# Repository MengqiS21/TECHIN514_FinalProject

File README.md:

# Pet Activity & Proximity Tracker

A wearable sensing tag for pets and a tabletop display that visualizes daily activity and proximity-based companionship.  
The system is designed as a calm, ambient tool that supports reflection rather than real-time alerts, helping pet owners understand patterns of activity and togetherness over the course of a day. By translating sensed data into a physical gauge, the project emphasizes presence and routine over precise tracking or notifications.

## 1. Overview

### What it does
This project consists of a lightweight sensing device attached to a pet’s collar and a tabletop display device placed in the home. The system tracks the pet’s activity level and estimates proximity to the owner throughout the day, visualizing overall “bond time” using a physical gauge instead of a screen.

### General system sketch

### Repository structure
```text
TECHIN514_FinalProject/
├─ README.md
├─ archive/
│  └─ root_pio_legacy/          # early PlatformIO prototype
├─ docs/
│  ├─ images/                   # system diagrams and renders
│  ├─ datasheets/               # component datasheets
│  └─ gantt.xlsx
├─ firmware/
│  ├─ sensor_tag/               # collar sensing tag firmware (ESP32-C3)
│  │  ├─ src/
│  │  ├─ include/
│  │  ├─ lib/
│  │  └─ test/
│  └─ display_meter/            # tabletop display firmware (ESP32-C3)
│     ├─ src/
│     ├─ include/
│     ├─ lib/
│     └─ test/
└─ hardware/
   ├─ pcb/
   │  ├─ sensor_tag/            # sensor-tag PCB project files
   │  ├─ display/               # display PCB project files
   │  ├─ legacy_pcb/            # older PCB iteration
   │  └─ PCB Production/        # Gerbers and drill files
   └─ enclosure/                # enclosure CAD/STL/STEP files
```

## 2. Sensing Device (Pet Collar Tag)

### Description
The sensing device is a lightweight tag mounted on a pet’s collar that detects motion and estimates proximity to the owner. It classifies activity levels (resting, walking, high activity) and tracks how much time the pet spends near the display device without using GPS.

### Detailed sensing device sketch

### How it works
- An onboard accelerometer detects motion patterns to estimate activity intensity.
- The sensor samples IMU acceleration for a short time window and computes a compact activity score.
- Summarized data is transmitted periodically to the display device via BLE.

### Signal Processing / Machine Learning (Current Implementation)
- The current system uses **lightweight signal processing**, not a trained machine learning model.
- In `firmware/sensor_tag/src/main.cpp`, the tag samples acceleration for a **1.5 s window** with a **40 ms** sample period.
- For each sample, it computes motion magnitude proxy `|ax| + |ay| + |az|`, averages over the window, and maps it linearly to a **0-100** activity score (`3g -> 100`, clamped).
- This activity score is sent to the display via BLE and mapped to motor/LED behavior.

### Accuracy Numbers (Current Status)
- A labeled dataset evaluation is not yet included in this repository.
- Therefore, formal ML metrics such as **accuracy / precision / recall / F1** are currently **N/A (not reported yet)**.

### Sensors and components (with part numbers)
- **Accelerometer:** ADXL345 (Analog Devices, 3-axis digital accelerometer)
- **Microcontroller + BLE:** ESP32-C3-MINI-1
- **Battery:** CR2032 coin cell *or* 150–300 mAh LiPo battery
- **Power management:** MCP1700 low-dropout regulator
- **Optional proximity aid:** Onboard ESP32 BLE RSSI (no extra sensor required)

## 3. Display Device (Bond Meter)

### Description
The display device is a tabletop “bond meter” that physically visualizes the pet’s daily activity and proximity time using a stepper-motor-driven gauge needle. An LED provides real-time feedback when the pet is nearby, and a button allows users to switch display modes or acknowledge the status.

### Detailed display device sketch

### How it works
- The display receives summarized activity and proximity data via BLE.
- The microcontroller maps daily totals to a gauge needle position using a stepper motor.
- The LED indicates current proximity state (e.g., pet nearby vs away).
- The button toggles display modes (activity vs proximity) or resets daily tracking.

### Components (with part numbers)
- **Microcontroller + BLE:** ESP32-C3-MINI-1
- **Stepper motor:** 28BYJ-48 stepper motor
- **Motor driver:** ULN2003 stepper driver
- **LED:** WS2812B single RGB LED *or* standard 5mm LED
- **Button:** Standard tact switch
- **Battery:** 500–1200 mAh LiPo battery

## 4. System Communication & Data Flow

### Wireless communication overview

### Detailed system diagram

## Notes on Power and Feasibility
Both devices are battery-powered and optimized for low-duty-cycle operation. The sensing device minimizes power usage through aggressive sleep scheduling, while the display device uses short stepper motor movements and infrequent updates to maintain reasonable battery life.

### Schematic and PCB Design

### PCB Production

### Battery Life Estimation
https://docs.google.com/spreadsheets/d/1o1SAS0YDETgxqNn3ZR0W69rIJqL8Xmiv9CGHoeJ4H2A/edit?usp=sharing

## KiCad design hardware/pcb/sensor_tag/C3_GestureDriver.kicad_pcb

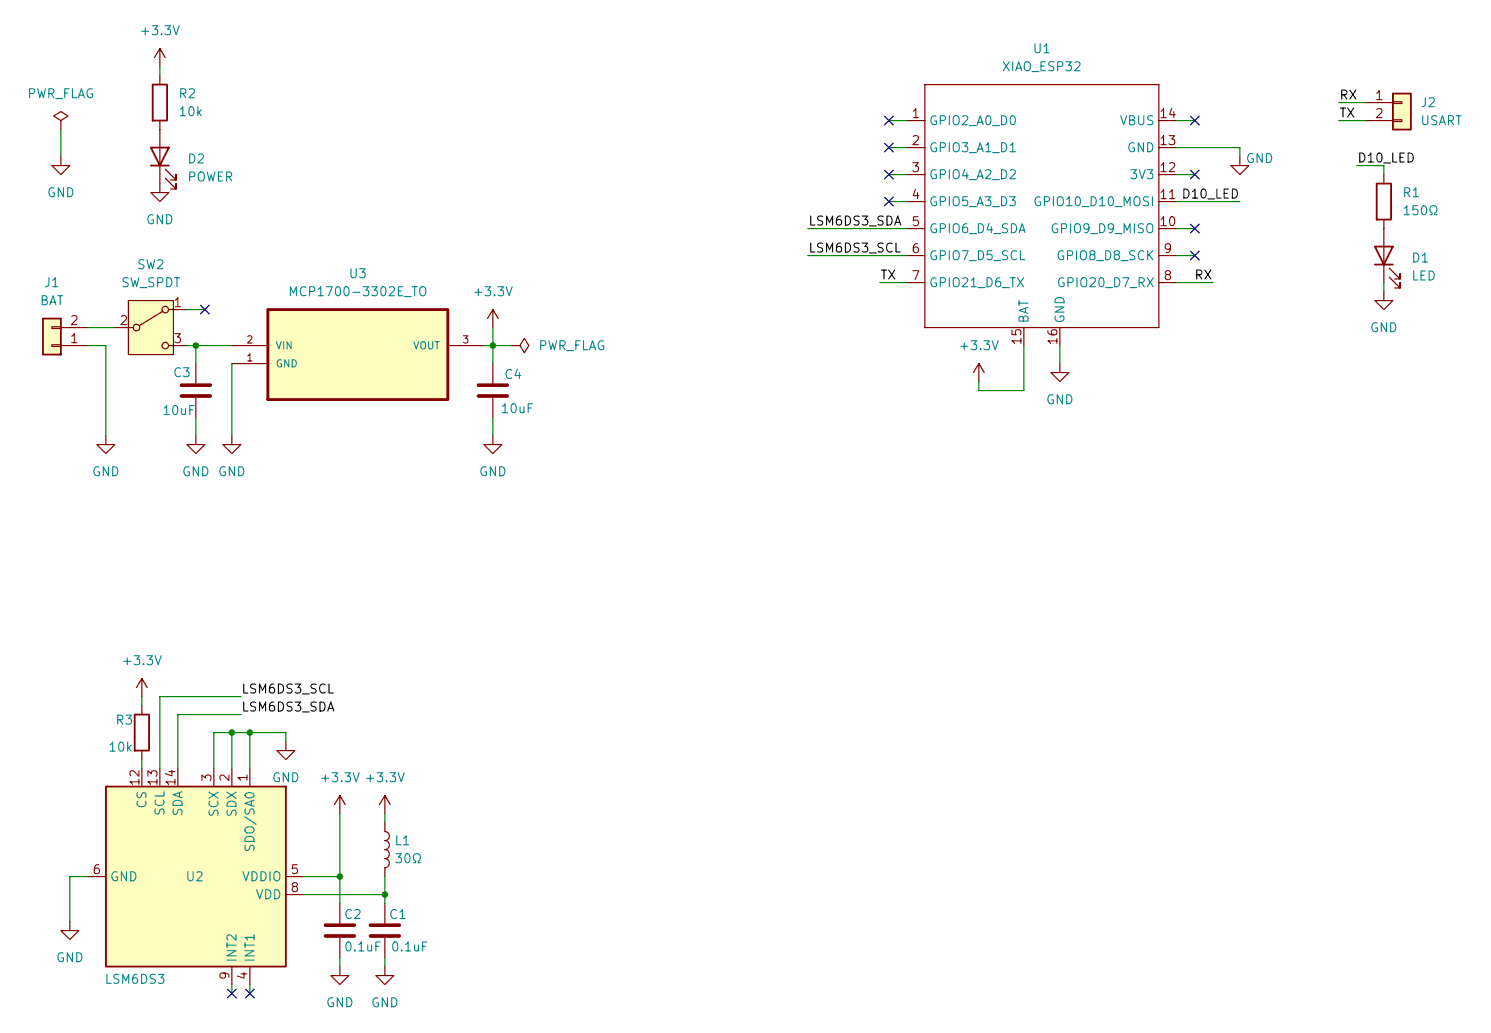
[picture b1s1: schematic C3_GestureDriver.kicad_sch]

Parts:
C1, C2: 0.1uF; C_0603_1608Metric
C3, C4: 10uF; C_0603_1608Metric
D1: LED; LED_0603_1608Metric
D2: POWER; LED_0603_1608Metric
J1: BAT; JST_PH_B2B-PH-K_1x02_P2.00mm_Vertical
J2: USART; PinHeader_1x02_P2.54mm_Vertical
L1: 30Ω; L_0603_1608Metric
R1: 150Ω; R_0603_1608Metric
R2, R3: 10k; R_0603_1608Metric
SW2: SW_SPDT; SS-12D00-Gx
U1: XIAO_ESP32
U2: LSM6DS3; LGA-14_3x2.5mm_P0.5mm_LayoutBorder3x4y
U3: MCP1700-3302E_TO; TO127P254X495-3; MPN MCP1700-3302E/TO

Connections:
+3.3V: C2.1, C4.1, L1.1, R2.1, R3.1, U1.15 (BAT), U2.5 (VDDIO), U3.3 (VOUT)
/D10_LED: R1.1, U1.11 (GPIO10_D10_MOSI)
/LSM6DS3_SCL: U1.6 (GPIO7_D5_SCL), U2.13 (SCL)
/LSM6DS3_SDA: U1.5 (GPIO6_D4_SDA), U2.14 (SDA)
/RX: J2.1, U1.8 (GPIO20_D7_RX)
/TX: J2.2, U1.7 (GPIO21_D6_TX)
GND: C1.2, C2.2, C3.2, C4.2, D1.1 (K), D2.1 (K), J1.1, U1.13 (GND), U1.16 (GND), U2.1 (SDO/SA0), U2.2 (SDX), U2.3 (SCX), U2.6 (GND), U2.7 (GND), U3.1 (GND)
unnamed: D1.2 (A), R1.2
unnamed: D2.2 (A), R2.2
unnamed: J1.2, SW2.2 (B)
unnamed: C3.1, SW2.3 (C), U3.2 (VIN)
unnamed: R3.2, U2.12 (CS)
unnamed: C1.1, L1.2, U2.8 (VDD)

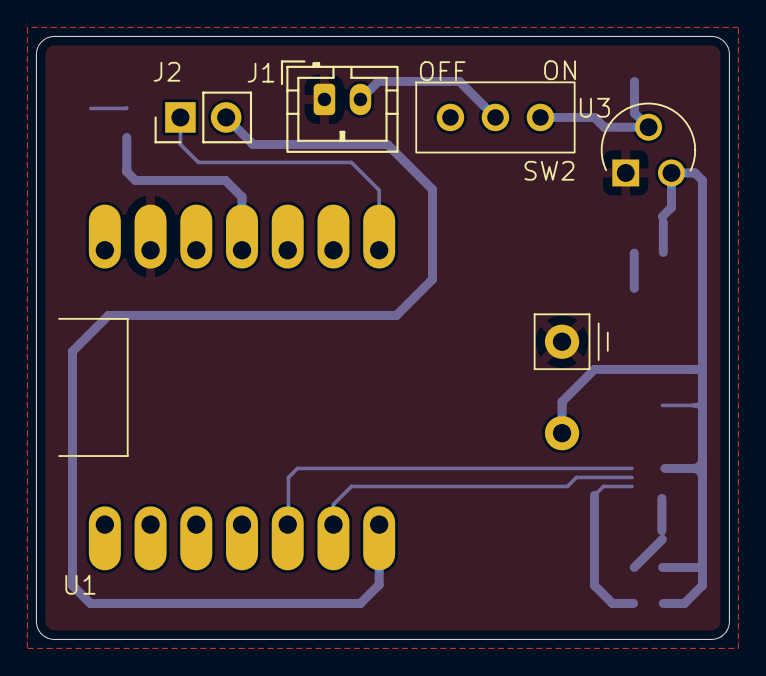
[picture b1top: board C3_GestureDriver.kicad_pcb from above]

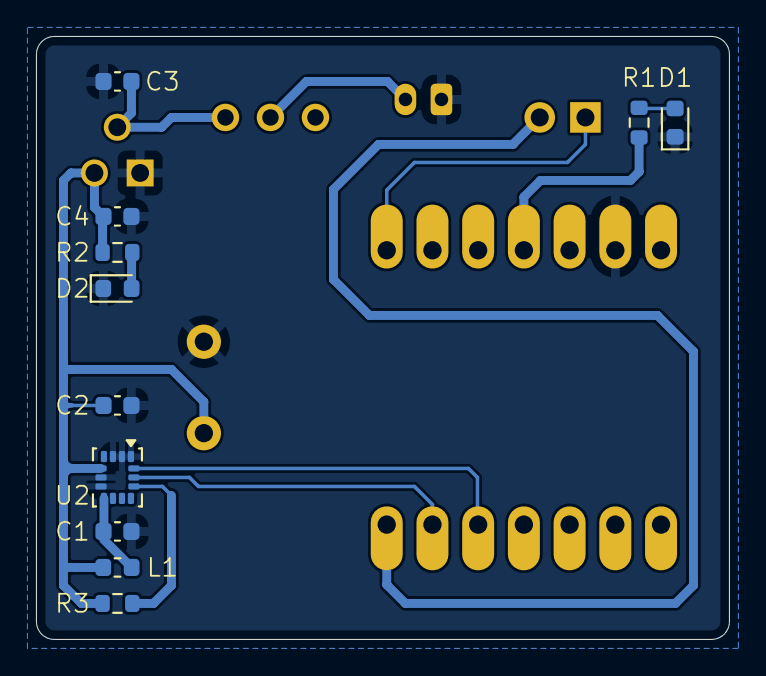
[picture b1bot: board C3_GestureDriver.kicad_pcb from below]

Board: 2 copper layers, 38.5 x 33.5 mm, 16 parts (11 on the bottom side), 13 nets.

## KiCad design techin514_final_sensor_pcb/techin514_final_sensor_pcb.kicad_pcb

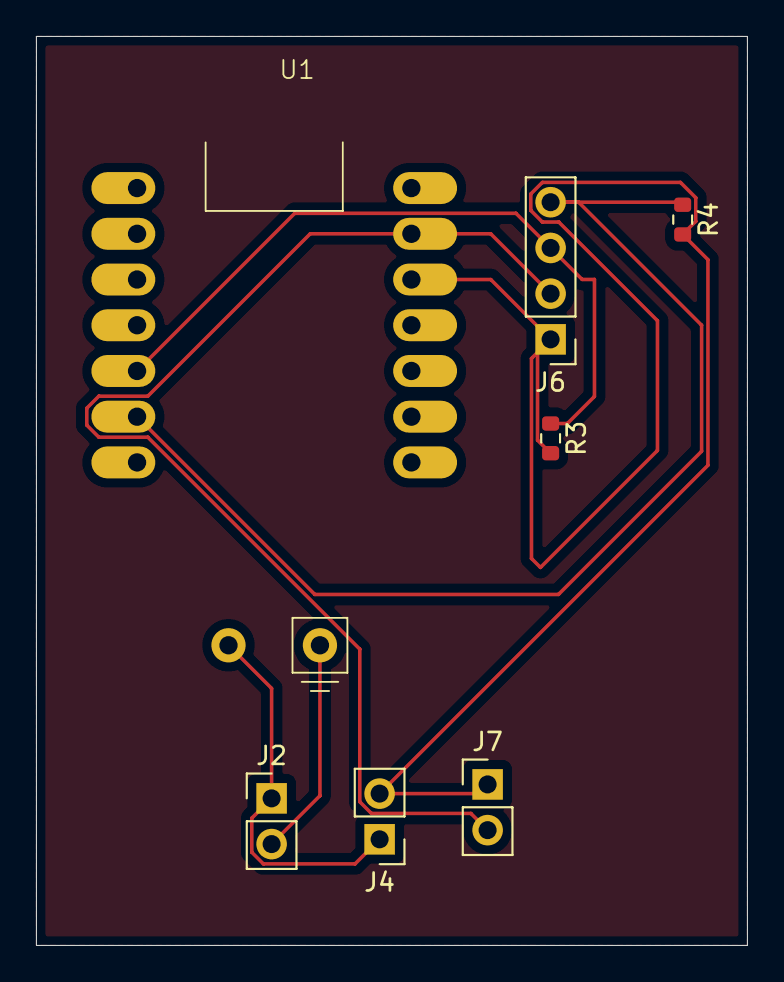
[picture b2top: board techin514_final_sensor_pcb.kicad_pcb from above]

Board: 2 copper layers, 39.5 x 50.5 mm, 7 parts (0 on the bottom side), 6 nets.

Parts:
J2: J_BAT; PinHeader_1x02_P2.54mm_Vertical
J4: J_LDO; PinHeader_1x02_P2.54mm_Vertical
J6: J_IMU; PinHeader_1x04_P2.54mm_Vertical
J7: J_PWR; PinHeader_1x02_P2.54mm_Vertical
R3, R4: 4.7kOhm; R_0603_1608Metric
U1: XIAO_ESP32

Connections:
unnamed: J2.2 (GND), U1.16 (-BATT)
unnamed: J2.1 (VBAT), J4.1 (VBAT), U1.15 (+BATT)
unnamed: J4.2 (3V3), J6.1 (3V3), J7.1 (3V3), R3.2, R4.2, U1.12 (3V3)
unnamed: J6.2 (GND), J7.2 (GND), U1.13 (GND)
unnamed: J6.4 (SCL), R4.1, U1.6 (GPIO6_A5_D5_SCL)
unnamed: J6.3 (SDA), R3.1, U1.5 (GPIO4_A3_D3_SDA)

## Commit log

2026-01-18 restore original "test"
2026-01-19 upload images
2026-01-19 datasheets upload
2026-01-19 update photos
2026-01-20 update intro
2026-01-25 add kicad
2026-01-25 update BOM
2026-01-26 update schematic
2026-01-27 update schematic and pcb
2026-01-28 update pcb
2026-01-28 update schematic pdf
2026-01-31 updated drl
2026-01-31 upload gcb files
2026-02-02 upload pcb and schematic pictures
2026-02-04 updated schematic and PCB
2026-02-04 updated PCB
2026-02-05 upload datesheet
2026-02-08 update ble
2026-02-12 PCB enclosure
2026-02-25 update code
2026-02-28 update structure
2026-03-02 update sensor code
2026-03-07 update everything
2026-03-08 update images
2026-03-08 update display pin
2026-03-08 update slide
2026-03-08 update sensor enclosure
